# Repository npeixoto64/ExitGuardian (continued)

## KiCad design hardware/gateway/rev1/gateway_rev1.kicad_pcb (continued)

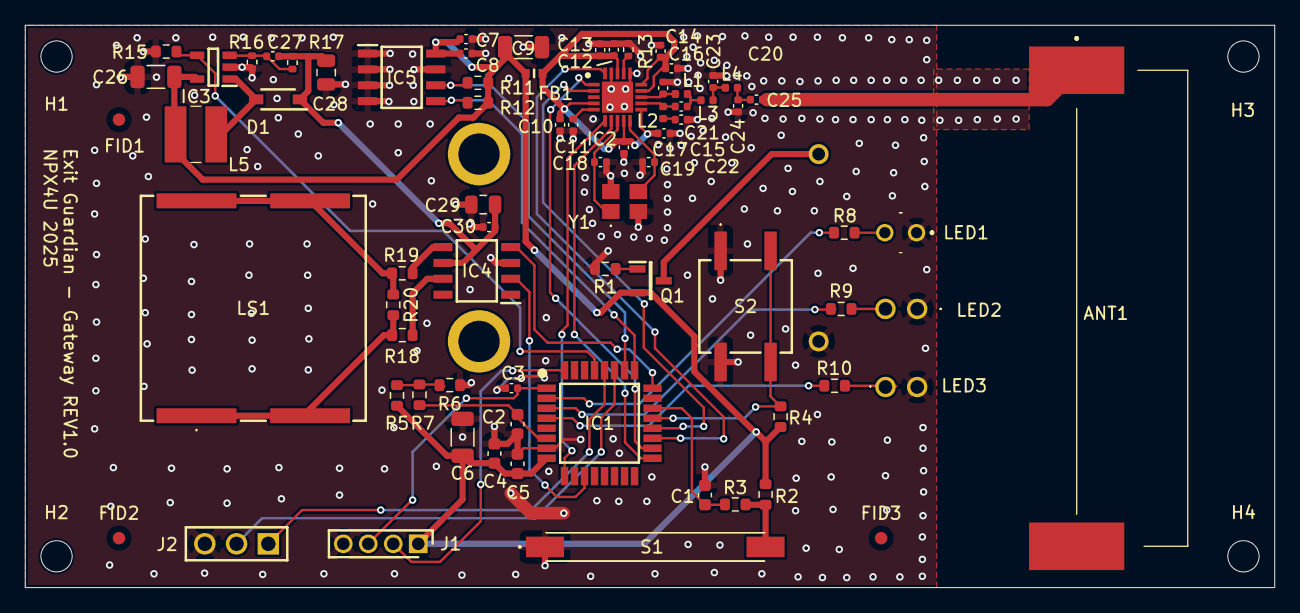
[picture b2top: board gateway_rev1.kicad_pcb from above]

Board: 2 copper layers, 100.0 x 45.0 mm, 80 parts (1 on the bottom side), 48 nets.

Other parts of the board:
FID1, FID2, FID3: Fiducial; Fiducial_1mm_Mask2mm

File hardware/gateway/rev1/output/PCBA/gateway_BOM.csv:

Designator,Qty,Value,Package,Manufacturer,Manufacturer Part Number,Mouser Part Number,Supplier Link
ANT1,1,ANT-433-HESM,MyParts:ANT433HESM,,,712-ANT-433-HESM,
"C1,C2,C5",3,100nF,Capacitor_SMD:C_0603_1608Metric,Taiyo Yuden,MAJCH168BB7104KT,963-MAJCH168BB7104KT,https://pt.mouser.com/ProductDetail/TAIYO-YUDEN/MAJCH168BB71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
C3,1,10nF,Capacitor_SMD:C_0402_1005Metric,Murata,GXT155R71C103KE01D,81-GXT155R71C103KE1D,https://pt.mouser.com/ProductDetail/Murata-Electronics/GXT15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
C4,1,1uF,Capacitor_SMD:C_0603_1608Metric,Yageo,CC603KRX5R6BB105 ,603-CC603KRX5R6BB105 ,https://pt.mouser.com/ProductDetail/YAGEO/CC0603KRX5R6BB105?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
"C6,C9",2,"47uF, 6.3V",Capacitor_SMD:C_1206_3216Metric,TAYO YUDEN,JMK325B7476MM-PR,963-JMK325B7476MM-PR,https://pt.mouser.com/ProductDetail/TAIYO-YUDEN/JMK325B7476M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
"C7,C13",2,1uF,Capacitor_SMD:C_0402_1005Metric,Murata,GXT155R60J105KE01D ,81-GXT155R60J105KE1D,https://pt.mouser.com/ProductDetail/Murata-Electronics/GXT15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
"C8,C10,C11,C12,C14,C15,C16,C17,C30",9,100nF,Capacitor_SMD:C_0402_1005Metric,Yageo,CC0402KRX7R7BB104,603-CC402KRX7R7BB104,https://pt.mouser.com/ProductDetail/YAGEO/CC0402KRX7R7BB104?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
"C18,C19",2,12pF,Capacitor_SMD:C_0402_1005Metric,Murata Electronics,GRM1555C1H120FA1D,81-GRM1555C1H120FA1D,https://pt.mouser.com/ProductDetail/Murata-Electronics/GRM15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
"C20,C22",2,3.9pF,Capacitor_SMD:C_0402_1005Metric,Murata,GRM1555C1E3R9CA1D,81-GRM1555C1E3R9CA1D,https://pt.mouser.com/ProductDetail/Murata-Electronics/GRM15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
"C21,C25",2,220pF,Capacitor_SMD:C_0402_1005Metric,Murata,GRM0225C1C221JA2L,81-GRM0225C1C221JA2L,https://pt.mouser.com/ProductDetail/Murata-Electronics/GRM02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
C23,1,8.2pF,Capacitor_SMD:C_0402_1005Metric,Murata,GCQ0335C1H8R2WB1D,81-GCQ0335C1H8R2WB1D,https://pt.mouser.com/ProductDetail/Murata-Electronics/GCQ03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
C24,1,5.6pF,Capacitor_SMD:C_0402_1005Metric,Murata,GCQ0335C1H5R6BB1D,81-GCQ0335C1H5R6BB1D,https://pt.mouser.com/ProductDetail/Murata-Electronics/GCQ03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
C26,1,"22uF, 6.3V",Capacitor_SMD:C_1206_3216Metric,Murata,GGM31CD70J226KE02L,81-GGM31CD70J226KE2L,https://pt.mouser.com/ProductDetail/Murata-Electronics/GGM31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
C27,1,4.7pF,Capacitor_SMD:C_0402_1005Metric,Murata,GCM1555C2A4R7BE02D,81-GCM1555C2A4R7BE2D,https://pt.mouser.com/ProductDetail/Murata-Electronics/GCM15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
"C28,C29",2,"4.7uF, 25V",Capacitor_SMD:C_0805_2012Metric,Taiyo Yuden,MCAST21GBC7475KTCA01,963-MCAST21GBC7475KT,https://pt.mouser.com/ProductDetail/TAIYO-YUDEN/MCAST21GBC74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
D1,1,MBR0520LT3G,MyParts:SOD3716X135N,onsemi,MBR0520LT3G,863-MBR0520LT3G,https://www.mouser.co.uk/ProductDetail/onsemi/MBR0520LT3G?qs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
FB1,1,BLM18KG601SN1D,MyParts:BLM18SP221SN1B,Murata Electronics,BLM18KG601SN1D,81-BLM18KG601SN1D,https://www.mouser.co.uk/ProductDetail/Murata-Electronics/BL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
IC1,1,STM8L151K4T6,MyParts:QFP80P900X900X160-32N,STMicroelectronics,STM8L151K4T6,511-STM8L151K4T6,https://www.mouser.co.uk/ProductDetail/STMicroelectronics/ST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
IC2,1,CC1101RGPR,MyParts:QFN50P400X400X100-21N-D,Texas Instruments,CC1101RGPR,595-CC1101RGPR,https://www.mouser.co.uk/ProductDetail/Texas-Instruments/CC1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
IC3,1,LT1615ES5-1#TRMPBF,MyParts:SOT95P280X100-5N,Analog Devices,LT1615ES5-1#TRMPBF,584-1615ES5-1TRMPBF,https://www.mouser.co.uk/ProductDetail/Analog-Devices/LT1615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
IC4,1,MIC4427YM,MyParts:SOIC127P599X173-8N,Microchip,MIC4427YM,998-MIC4427YM,https://www.mouser.co.uk/ProductDetail/Microchip-Technology/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
IC5,1,MB85RC64TAPNF-G-BDERE1,MyParts:SOIC127P602X173-8N,Ramxeed,MB85RC64TAPNF-G-BDERE1,249-85C64TAPNFGBDR1,https://www.mouser.co.uk/ProductDetail/Fujitsu-Semiconductor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
J1,1,G8250041000YEU,MyParts:HDRV4W55P0X200_1X4_800X200X635P,Amphenol,G8250041000YEU,523-G8250041000YEU,https://www.mouser.co.uk/ProductDetail/Amphenol-Commercial-P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
J2,1,M20-9770342,MyParts:HDRV3W66P0X254_1X3_762X254X855P,Harwin,M20-9770342,855-M20-9770342,https://www.mouser.co.uk/ProductDetail/Harwin/M20-9770342?qs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
"L1,L2,L4",3,27nH,Inductor_SMD:L_0402_1005Metric,Murata,LQG15HS27NJ02D,81-LQG15HS27NJ02D,https://pt.mouser.com/ProductDetail/Murata-Electronics/LQG15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
L3,1,22nH,Inductor_SMD:L_0402_1005Metric,Murata,LQW15CA22NJ00D,81-LQW15CA22NJ00D,https://pt.mouser.com/ProductDetail/Murata-Electronics/LQW15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
L5,1,CD43NP-100MC,MyParts:CD43NP100MC,Sumida,CD43NP-100MC,851-CD43NP-100MC,https://www.mouser.co.uk/ProductDetail/Sumida/CD43NP-100MC?q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
LED1,1,WP710A10LVBC_D,MyParts:WP710A10LVBCD,Kingbright,WP710A10LVBC/D,604-WP710A10LVBCD,https://www.mouser.co.uk/ProductDetail/Kingbright/WP710A10LV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
LED2,1,TLHY4400-AS12Z,MyParts:TLHY4400AS12Z,Vishay,TLHY4400-AS12Z,78-TLHY4400-AS12Z,https://www.mouser.co.uk/ProductDetail/Vishay-Semiconductors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
LED3,1,TLHR4400-AS12Z,MyParts:TLHR4400AS12Z,Vishay,TLHR4400-AS12Z,78-TLHR4400-AS12Z,https://www.mouser.co.uk/ProductDetail/Vishay-Semiconductors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
LS1,1,PKMCS1818E20A0-R1,MyParts:PKMCS1818E20A0R1,Murata Electronics,PKMCS1818E20A0-R1,81-PKMCS1818E20A0-R1,https://www.mouser.co.uk/ProductDetail/Murata-Electronics/PK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
Q1,1,IRLML6402TRPBF,MyParts:SOT95P237X112-3N,Infineon,IRLML6402TRPBF,942-IRLML6402TRPBF,https://www.mouser.co.uk/ProductDetail/Infineon-Technologies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
"R1,R3,R15",3,100K,Resistor_SMD:R_0603_1608Metric,Vishay,MCT06030C1003FP5,594-MCT06030C1003FP5,https://pt.mouser.com/ProductDetail/Vishay-Beyschlag/MCT0603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
"R2,R5,R20",3,1M,Resistor_SMD:R_0603_1608Metric,Yageo,AR0603FR-071ML,603-AR0603FR-071ML,https://pt.mouser.com/ProductDetail/YAGEO/AR0603FR-071ML?qs=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
"R4,R11,R12",3,10K,Resistor_SMD:R_0603_1608Metric,Vishay,RCA060310K0JNEA,71-RCA060310K0JNEA,https://pt.mouser.com/ProductDetail/Vishay-Draloric/RCA06031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
R6,1,510K,Resistor_SMD:R_0603_1608Metric,Vishay,CRCW0603-510K,71-CRCW0603-510K,https://pt.mouser.com/ProductDetail/Vishay/CRCW0603510KFKTA?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
R7,1,1K,Resistor_SMD:R_0603_1608Metric,Yageo,SR0603JR-071KL,603-SR0603JR-071KL,https://pt.mouser.com/ProductDetail/YAGEO/SR0603JR-071KL?qs=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
R8,1,100,Resistor_SMD:R_0603_1608Metric,Vishay,CRCW0603100RJNEBC,71-CRCW0603100RJNEBC,https://pt.mouser.com/ProductDetail/Vishay/CRCW0603100RJNEBC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
"R9,R10",2,47,Resistor_SMD:R_0603_1608Metric,Panasonic,ERJ-S03J470V,667-ERJ-S03J470V,https://pt.mouser.com/ProductDetail/Panasonic/ERJ-S03J470V?q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
R13,1,56K,Resistor_SMD:R_0402_1005Metric,Panasonic,ERJ-PA2F5602X,667-ERJ-PA2F5602X,https://pt.mouser.com/ProductDetail/Panasonic/ERJ-PA2F5602X?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
R16,1,130K,Resistor_SMD:R_0402_1005Metric,Yageo,RC0402DR-07130KL,603-RC0402DR-07130KL,https://pt.mouser.com/ProductDetail/YAGEO/RC0402DR-07130KL?q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
R17,1,1.15M,Resistor_SMD:R_0402_1005Metric,Yageo,RC0402FR-071M15L,603-RC0402FR-071M15L,https://pt.mouser.com/ProductDetail/YAGEO/RC0402FR-071M15L?q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
"R18,R19",2,33R,Resistor_SMD:R_0603_1608Metric,Yageo,"SR0603JR-7T33RL,SR0603JR-7T33RL ","603-SR0603JR-7T33RL,603-SR0603JR-7T33RL ",https://pt.mouser.com/ProductDetail/YAGEO/SR0603JR-7T33RL?qs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
S1,1,MASM-14R-8-10,MyParts:MASM14R810,LITTELFUSE,MASM-14R-8-10,934-MASM-14R-8-10,https://www.mouser.co.uk/ProductDetail/Littelfuse/MASM-14R-8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
S2,1,TL6120DF160QG,MyParts:TL6120DF160QG,E-Switch,TL6120DF160QG,612-TL6120DF160QG,https://www.mouser.co.uk/ProductDetail/E-Switch/TL6120DF160Q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
U1,1,2462,MyParts:2462,Keystone Electronics,2462,534-2462,https://www.mouser.co.uk/ProductDetail/Keystone-Electronics/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
Y1,1,NX3225GA-26.000M-STD-CRG-2,MyParts:NX3225GA26000MSTDCRG2,NDK,NX3225GA-26.000M-STD-CRG-2,344-NX3225GA26MSTRG2,https://www.mouser.co.uk/ProductDetail/NDK/NX3225GA-26.000M-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

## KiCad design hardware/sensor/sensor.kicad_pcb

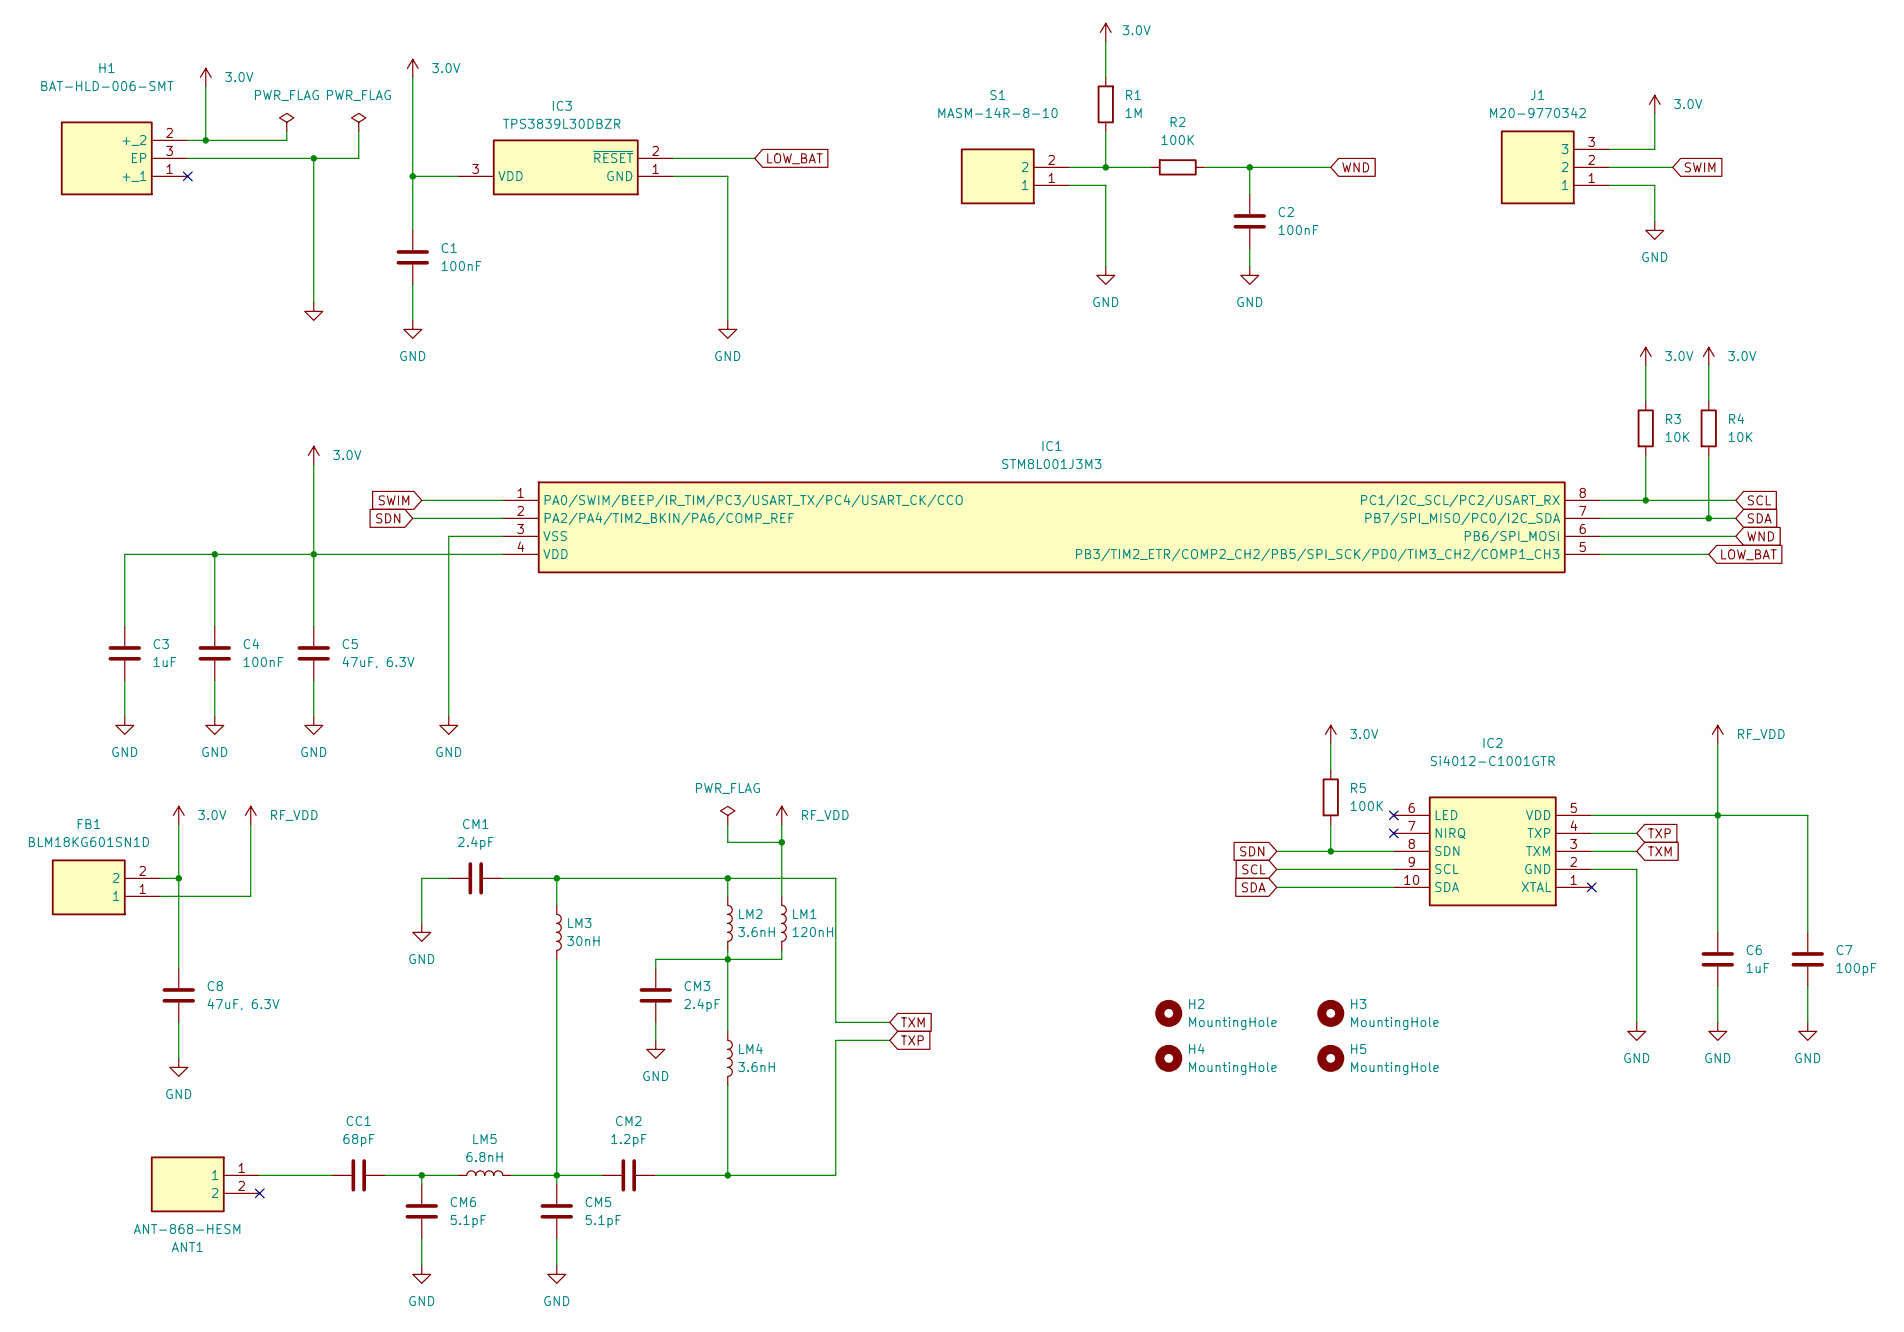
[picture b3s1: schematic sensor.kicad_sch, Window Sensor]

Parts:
ANT1: ANT-868-HESM; Mouser Part Number 712-ANT-868-HESM
C1, C2, C4: 100nF; C_0603_1608Metric; Mouser Part Number 81-GCJ188R72A104KA1D
C3, C6: 1uF; C_0603_1608Metric; Mouser Part Number 963-MBASE168SB7105KT
C5, C8: 47uF, 6.3V; C_1206_3216Metric; Mouser Part Number 963-JMK325B7476MM-PR
C7: 100pF; C_0603_1608Metric; Mouser Part Number 77-VJ0603Y101MXQCBC
CC1: 68pF; C_0402_1005Metric; Mouser Part Number 81-GRM1555C1H680FA1J
CM1, CM3: 2.4pF; C_0402_1005Metric; Mouser Part Number 81-GRM1555C1H2R4WA1D
CM2: 1.2pF; C_0402_1005Metric; Mouser Part Number 81-GRM1555C1H1R2WA1D
CM5, CM6: 5.1pF; C_0402_1005Metric; Mouser Part Number 81-GRM1555C1H5R1WA1D
FB1: BLM18KG601SN1D; BLM18SP221SN1B; Mouser Part Number 81-BLM18KG601SN1D
H1: BAT-HLD-006-SMT; BATHLD006SMT; Mouser Part Number 712-BAT-HLD-006-SMT
H2, H3, H4, H5: MountingHole; MountingHole_2.5mm
IC1: STM8L001J3M3; SOIC127P600X175-8N; Mouser Part Number 511-STM8L001J3M3
IC2: Si4012-C1001GTR; SOP50P490X110-10N; Mouser Part Number 634-SI4012-C1001GTR
IC3: TPS3839L30DBZR; SOT95P237X112-3N; Mouser Part Number 595-TPS3839L30DBZR
J1: M20-9770342; HDRV3W66P0X254_1X3_762X254X855P; Mouser Part Number 855-M20-9770342
LM1: 120nH; L_0603_1608Metric; Mouser Part Number 994-0603HP-R12XGLU
LM2, LM4: 3.6nH; L_0402_1005Metric; Mouser Part Number 994-0402HP-3N6XGRW
LM3: 30nH; L_0402_1005Metric; Mouser Part Number 994-0402HP-30NXJRW
LM5: 6.8nH; L_0402_1005Metric; Mouser Part Number 994-0402HP-6N8XGRW
R1: 1M; R_0603_1608Metric; Mouser Part Number 755-SFR03EZPJ105
R2, R5: 100K; R_0603_1608Metric; Mouser Part Number 71-RCA0603100KJNEA
R3, R4: 10K; R_0603_1608Metric; Mouser Part Number 603-AC0603JR-7W10KL
S1: MASM-14R-8-10; MASM14R810; Mouser Part Number 934-MASM-14R-8-10

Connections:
3.0V: C1.1, C3.1, C4.1, C5.1, C8.1, FB1.2, H1.2 (+_2), IC1.4 (VDD), IC3.3 (VDD), J1.3, R1.2, R3.1, R4.1, R5.1
GND: C1.2, C2.2, C3.2, C4.2, C5.2, C6.2, C7.2, C8.2, CM1.2, CM3.2, CM5.2, CM6.2, H1.3 (EP), IC1.3 (VSS), IC2.2 (GND), IC3.1 (GND), J1.1, S1.1
LOW_BAT: IC1.5 (PB3/TIM2_ETR/COMP2_CH2/PB5/SPI_SCK/PD0/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), IC3.2 (~RESET)
unnamed: ANT1.1, CC1.1
unnamed: CC1.2, CM6.1, LM5.1
unnamed: CM2.1, CM5.1, LM3.2, LM5.2
unnamed: CM3.1, LM1.2, LM2.2, LM4.1
unnamed: R1.1, R2.2, S1.2
RF_VDD: C6.1, C7.1, FB1.1, IC2.5 (VDD), LM1.1
SCL: IC1.8 (PC1/I2C_SCL/PC2/USART_RX), IC2.9 (SCL), R3.2
SDA: IC1.7 (PB7/SPI_MISO/PC0/I2C_SDA), IC2.10 (SDA), R4.2
SDN: IC1.2 (PA2/PA4/TIM2_BKIN/PA6/COMP_REF), IC2.8 (SDN), R5.2
SWIM: IC1.1 (PA0/SWIM/BEEP/IR_TIM/PC3/USART_TX/PC4/U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), J1.2
TXM: CM1.1, IC2.3 (TXM), LM2.1, LM3.1
TXP: CM2.2, IC2.4 (TXP), LM4.2
WND: C2.1, IC1.6 (PB6/SPI_MOSI), R2.1

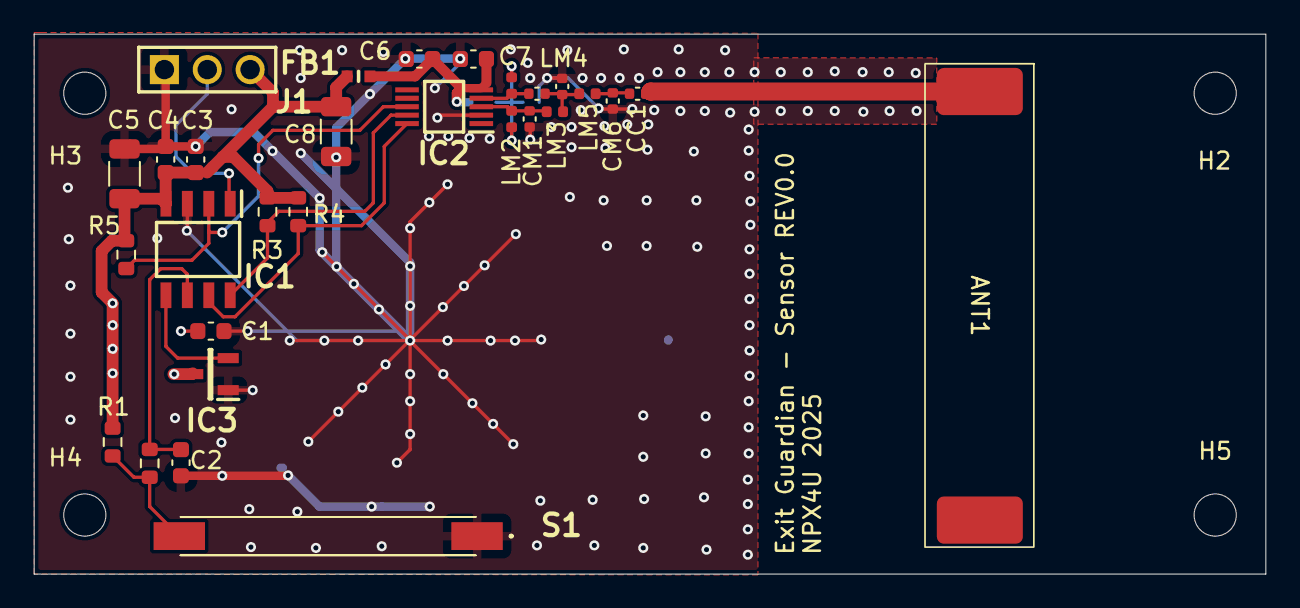
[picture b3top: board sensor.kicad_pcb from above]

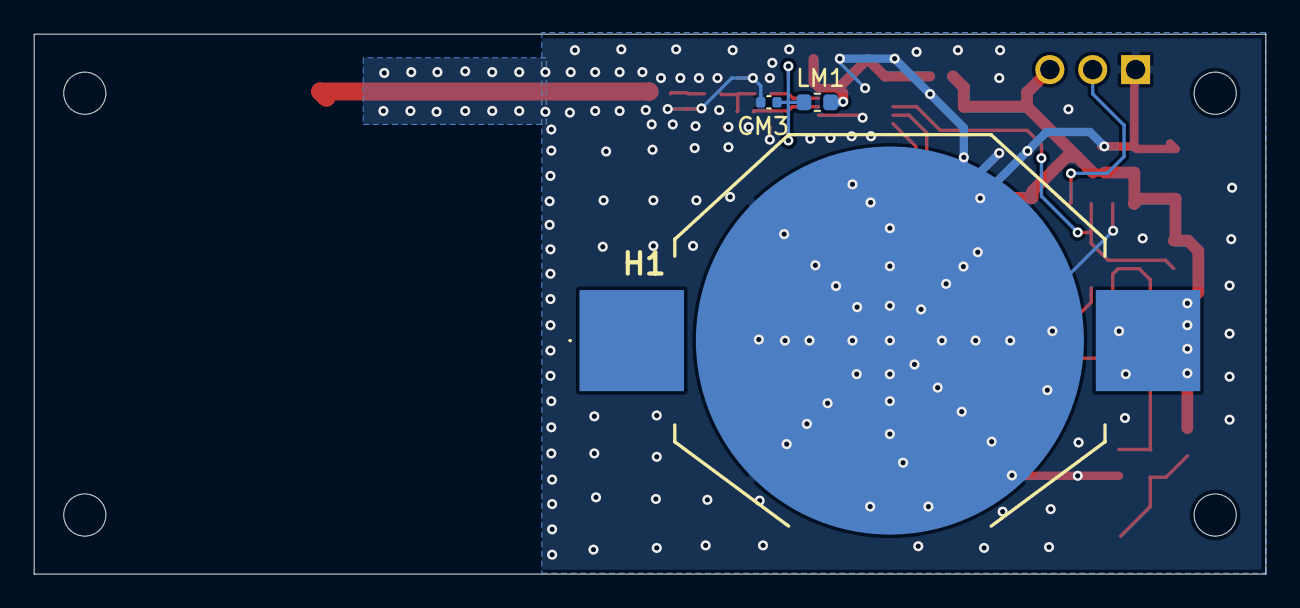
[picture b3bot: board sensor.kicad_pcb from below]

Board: 2 copper layers, 73.0 x 32.0 mm, 36 parts (3 on the bottom side), 16 nets.

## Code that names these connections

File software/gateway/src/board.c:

/**
 * @file board.c
 * @brief Board support package implementation: clocks, peripherals and power.
 */
#include "board.h"

#include "stm8l15x_clk.h"
#include "stm8l15x_gpio.h"
#include "stm8l15x_adc.h"
#include "stm8l15x_i2c.h"
#include "stm8l15x_spi.h"
#include "stm8l15x_usart.h"
#include "stm8l15x_tim1.h"
#include "stm8l15x_tim4.h"
#include "stm8l15x_exti.h"
#include "stm8l15x_iwdg.h"
#include "cc1101.h"

/** @brief Configure the system clock to 16 MHz from the internal HSI. */
static void clock_init(void)
{
  /* 16 MHz (HSI with divider 1) */
  CLK_HSICmd(ENABLE);
  while (CLK_GetFlagStatus(CLK_FLAG_HSIRDY) == RESET);
  CLK_SYSCLKSourceConfig(CLK_SYSCLKSource_HSI);
  CLK_SYSCLKDivConfig(CLK_SYSCLKDiv_1);
}

/**
 * @brief Configure all GPIOs used on the board.
 *
 * Unused pins are pulled up to minimise leakage; peripheral pins are set to
 * the modes required by I2C, SPI, USART, TIM1 PWM and the EXTI inputs.
 */
static void gpio_init(void)
{
  /* Unused pins as input pull-up to minimise leakage. */
  GPIO_Init(GPIOA, GPIO_Pin_5, GPIO_Mode_In_PU_No_IT);
  GPIO_Init(GPIOB, GPIO_Pin_0, GPIO_Mode_In_PU_No_IT);
  GPIO_Init(GPIOB, GPIO_Pin_1, GPIO_Mode_In_PU_No_IT);
  GPIO_Init(GPIOB, GPIO_Pin_2, GPIO_Mode_In_PU_No_IT);
  GPIO_Init(GPIOB, GPIO_Pin_3, GPIO_Mode_In_PU_No_IT);
  GPIO_Init(GPIOC, GPIO_Pin_5, GPIO_Mode_In_PU_No_IT);
  GPIO_Init(GPIOC, GPIO_Pin_6, GPIO_Mode_In_PU_No_IT);
  GPIO_Init(GPIOD, GPIO_Pin_6, GPIO_Mode_In_PU_No_IT);

  /* PA6 ADC input (floating). */
  GPIO_Init(GPIOA, GPIO_Pin_6, GPIO_Mode_In_FL_No_IT);

  /* I2C: PC0 SDA, PC1 SCL (open-drain). */
  GPIO_Init(GPIOC, GPIO_Pin_0, GPIO_Mode_Out_OD_HiZ_Fast);
  GPIO_Init(GPIOC, GPIO_Pin_1, GPIO_Mode_Out_OD_HiZ_Fast);

  /* SPI: PB4 NSS, PB5 SCK, PB6 MOSI, PB7 MISO. */
  GPIO_Init(GPIOB, GPIO_Pin_4, GPIO_Mode_Out_PP_High_Fast);
  GPIO_Init(GPIOB, GPIO_Pin_5, GPIO_Mode_Out_PP_High_Fast);
  GPIO_Init(GPIOB, GPIO_Pin_6, GPIO_Mode_Out_PP_High_Fast);
  GPIO_Init(GPIOB, GPIO_Pin_7, GPIO_Mode_In_FL_No_IT);

  /* USART: PC2 TX, PC3 RX. */
  GPIO_Init(GPIOC, GPIO_Pin_2, GPIO_Mode_Out_PP_High_Fast);
  GPIO_Init(GPIOC, GPIO_Pin_3, GPIO_Mode_In_FL_No_IT);

  /* TIM1 differential PWM: PD7 CH1, PD2 CH1N. */
  GPIO_Init(GPIOD, GPIO_Pin_7, GPIO_Mode_Out_PP_High_Fast);
  GPIO_Init(GPIOD, GPIO_Pin_2, GPIO_Mode_Out_PP_High_Fast);

  /* External interrupt inputs. */
  GPIO_Init(IRQ_CC1101_PORT, IRQ_CC1101_PIN, GPIO_Mode_In_FL_IT);
  GPIO_Init(PUSH_BTN_PORT,   PUSH_BTN_PIN,   GPIO_Mode_In_FL_IT);
  GPIO_Init(REED_DOOR_PORT,  REED_DOOR_PIN,  GPIO_Mode_In_FL_IT);

  /* LEDs + spare PC4 output. */
  GPIO_Init(LED_B_PORT, LED_B_PIN, GPIO_Mode_Out_PP_Low_Fast);
  GPIO_Init(LED_Y_PORT, LED_Y_PIN, GPIO_Mode_Out_PP_Low_Fast);
  GPIO_Init(LED_R_PORT, LED_R_PIN, GPIO_Mode_Out_PP_Low_Fast);
  GPIO_Init(BUZZER_EN_PORT, BUZZER_EN_PIN, GPIO_Mode_Out_PP_Low_Fast);

  GPIO_ResetBits(LED_B_PORT, LED_B_PIN);
  GPIO_ResetBits(LED_Y_PORT, LED_Y_PIN);
  GPIO_ResetBits(LED_R_PORT, LED_R_PIN);
  GPIO_ResetBits(BUZZER_EN_PORT, BUZZER_EN_PIN);
}

/** @brief Configure EXTI edge sensitivity for CC1101, button and reed inputs. */
static void exti_init(void)
{
  EXTI_SetPinSensitivity(IRQ_CC1101_EXTI, EXTI_Trigger_Falling);
  EXTI_SetPinSensitivity(PUSH_BTN_EXTI,   EXTI_Trigger_Rising_Falling);
  EXTI_SetPinSensitivity(REED_DOOR_EXTI,  EXTI_Trigger_Rising_Falling);
}

/** @brief Millisecond tick counter, incremented by @ref board_systick_irq. */
static volatile uint16_t s_tick_ms = 0;

/** @brief Configure TIM4 to generate a 1 kHz periodic update interrupt. */
static void systick_init(void)
{
  /* 16 MHz / 128 = 125 kHz; period 125 -> 1 ms tick. */
  CLK_PeripheralClockConfig(CLK_Peripheral_TIM4, ENABLE);
  TIM4_DeInit();
  TIM4_TimeBaseInit(TIM4_Prescaler_128, 125U - 1U);
  TIM4_ClearITPendingBit(TIM4_IT_Update);
  TIM4_ITConfig(TIM4_IT_Update, ENABLE);
  TIM4_Cmd(ENABLE);
}

uint16_t board_get_tick_ms(void)
{
  uint16_t t;
  /* Atomic read: save CC (I0/I1), mask interrupts, restore on exit.
   * Safe to call from both thread and ISR context. */
  __asm__("push cc\n\tsim");
  t = s_tick_ms;
  __asm__("pop cc");
  return t;
}

void board_systick_irq(void)
{
  TIM4_ClearITPendingBit(TIM4_IT_Update);
  s_tick_ms++;
}

/** @brief Configure ADC1 single-conversion mode on channel 6 (PA6). */
static void adc_init(void)
{
  CLK_PeripheralClockConfig(CLK_Peripheral_ADC1, ENABLE);
  ADC_DeInit(ADC1);
  ADC_Init(ADC1, ADC_ConversionMode_Single, ADC_Resolution_12Bit, ADC_Prescaler_2);
  ADC_SamplingTimeConfig(ADC1, ADC_Group_SlowChannels, ADC_SamplingTime_384Cycles);
  ADC_Cmd(ADC1, ENABLE);
  ADC_ChannelCmd(ADC1, ADC_Channel_6, ENABLE);
}

/** @brief Configure I2C1 as master at 400 kHz for the FRAM device. */
static void i2c_init(void)
{
  CLK_PeripheralClockConfig(CLK_Peripheral_I2C1, ENABLE);
  I2C_DeInit(I2C1);
  I2C_Init(I2C1, 400000, 0x00, I2C_Mode_I2C, I2C_DutyCycle_2,
           I2C_Ack_Enable, I2C_AcknowledgedAddress_7bit);
  I2C_Cmd(I2C1, ENABLE);
}

/** @brief Configure SPI1 as 8-bit master, mode 0, for the CC1101. */
static void spi_init(void)
{
  CLK_PeripheralClockConfig(CLK_Peripheral_SPI1, ENABLE);
  SPI_DeInit(SPI1);
  SPI_Init(SPI1, SPI_FirstBit_MSB, SPI_BaudRatePrescaler_16, SPI_Mode_Master,
           SPI_CPOL_Low, SPI_CPHA_1Edge, SPI_Direction_2Lines_FullDuplex,
           SPI_NSS_Soft, 7);
  SPI_Cmd(SPI1, ENABLE);
}

/** @brief Configure USART1 for 9600 8N1 debug logging. */
static void uart_init(void)
{
  CLK_PeripheralClockConfig(CLK_Peripheral_USART1, ENABLE);
  USART_DeInit(USART1);
  USART_Init(USART1, (uint32_t)9600, USART_WordLength_8b, USART_StopBits_1,
             USART_Parity_No,
             (USART_Mode_TypeDef)(USART_Mode_Tx | USART_Mode_Rx));
  USART_Cmd(USART1, ENABLE);
}

/** @brief Configure TIM1 channel 1 / 1N differential PWM for the buzzer. */
static void pwm_init(void)
{
  CLK_PeripheralClockConfig(CLK_Peripheral_TIM1, ENABLE);
  TIM1_DeInit();
  TIM1_TimeBaseInit(7U, TIM1_CounterMode_Up, 1000U, 0U);
  TIM1_OC1Init(TIM1_OCMode_PWM1,
               TIM1_OutputState_Enable,
               TIM1_OutputNState_Enable,
               500U,
               TIM1_OCPolarity_High,
               TIM1_OCNPolarity_High,
               TIM1_OCIdleState_Reset,
               TIM1_OCNIdleState_Reset);
  TIM1_OC1PreloadConfig(ENABLE);
  TIM1_BDTRConfig(TIM1_OSSIState_Disable,
                  TIM1_LockLevel_Off,
                  0x10U,
                  TIM1_BreakState_Disable,
                  TIM1_BreakPolarity_Low,
                  TIM1_AutomaticOutput_Disable);
  TIM1_CtrlPWMOutputs(ENABLE);
}

/** @brief Start the independent watchdog with ~1.72 s timeout. */
static void iwdg_init(void)
{
  /* LSI is ~38 kHz. With prescaler 256 the IWDG tick is ~6.74 ms.
   * Reload 0xFF gives a watchdog timeout of ~1.72 s. */
  IWDG_Enable();
  IWDG_WriteAccessCmd(IWDG_WriteAccess_Enable);
  IWDG_SetPrescaler(IWDG_Prescaler_256);
  IWDG_SetReload(0xFF);
  IWDG_ReloadCounter();
}

void board_iwdg_refresh(void)
{
  IWDG_ReloadCounter();
}

void board_init(void)
{
  clock_init();
  gpio_init();
  exti_init();
  adc_init();
  i2c_init();
  spi_init();
  uart_init();
  pwm_init();
  systick_init();
  iwdg_init();

  enableInterrupts();
  
  cc1101_config_gfsk_433_rx_fixed(5);
}

void board_buzzer(uint8_t on)
{
  TIM1_Cmd(on ? ENABLE : DISABLE);
}

void board_enter_deep_sleep(void)
{
  /* Reduce current draw before HALT; wake source is EXTI on PD0/PD4/PD5. */
  ADC_Cmd(ADC1, DISABLE);
  I2C_Cmd(I2C1, DISABLE);
  SPI_Cmd(SPI1, DISABLE);
  USART_Cmd(USART1, DISABLE);

  enableInterrupts();
  halt();

  /* Restore peripherals after wake-up. */
  CLK_PeripheralClockConfig(CLK_Peripheral_ADC1, ENABLE);
  CLK_PeripheralClockConfig(CLK_Peripheral_I2C1, ENABLE);
  CLK_PeripheralClockConfig(CLK_Peripheral_SPI1, ENABLE);
  CLK_PeripheralClockConfig(CLK_Peripheral_USART1, ENABLE);
  CLK_PeripheralClockConfig(CLK_Peripheral_TIM1, ENABLE);

  ADC_Cmd(ADC1, ENABLE);
  I2C_Cmd(I2C1, ENABLE);
  SPI_Cmd(SPI1, ENABLE);
  USART_Cmd(USART1, ENABLE);
}

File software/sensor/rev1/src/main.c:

/**
 * @file main.c
 * @brief Application entry point and top-level interrupt handlers.
 */
#include <stdint.h>
#include <stdio.h>
#include "stm8l15x_itc.h"
#include "board.h"
#include "device_id.h"
#include "app_config.h"
#include "stm8l15x_gpio.h"
#include "stm8l15x_exti.h"
#include "stm8l15x_tim4.h"
#include "cc1101.h"
#include "log.h"

// ============================================================================
// Constants and Enums
// ============================================================================

// Status byte format:
// Bits 7-4: Battery capacity (high nibble)
// Bits 2-1: Button action (2 bits): 0=none, 1=force update, 2=pair, 3=unpair
// Bit 0:    Reed switch state
#define STATUS_REED_SW_BIT      0
#define STATUS_BTN_SHIFT        1
#define STATUS_BTN_MASK         0x03
#define STATUS_BATT_SHIFT       4
#define STATUS_BATT_MASK        0x0F

#define STATUS_SET_BATT(batt)   (((batt) & STATUS_BATT_MASK) << STATUS_BATT_SHIFT)
#define STATUS_SET_BTN(btn)     (((btn) & STATUS_BTN_MASK) << STATUS_BTN_SHIFT)
#define STATUS_SET_REED(reed)   (((reed) ? 1 : 0) << STATUS_REED_SW_BIT)

typedef enum {
    BTN_ACTION_NONE       = 0,
    BTN_ACTION_FORCE_UPD  = 1,
    BTN_ACTION_PAIR       = 2,
    BTN_ACTION_UNPAIR     = 3,
} button_action_t;

// Timing constants (in TIM2 ticks, 10ms per tick)
#define DEBOUNCE_TICKS              3    // 30ms debounce period
#define BTN_DOUBLE_PRESS_WINDOW     40   // 400ms max gap between clicks
#define BTN_LONG_PRESS_TICKS        80   // 800ms hold duration
#define LED_ON_HOLD_TICKS           50   // 500ms before auto-off
#define LED_ON_STARTUP_HOLD_TICKS   100  // 1000ms startup hold
#define LED_BLINK_HALF_PERIOD       20   // 200ms half-period for blink
#define LED_BLINK_COUNT             4    // 4 on-off cycles for low battery
#define LOW_BATTERY_THRESHOLD       3    // 0-15 scale
#define WWDG_COUNTER_MAX            0x7F // WWDG 7-bit counter max value (T[6:0])
#define WWDG_REFRESH_THRESHOLD      0x40 // Latest safe refresh point before watchdog reset (counter must stay >= 0x40)

// ============================================================================
// Global System State
// ============================================================================

static volatile uint8_t g_tim2_ticks = 0xFF;

// Button state variables
static struct {
    volatile uint8_t irq_flag;
    volatile uint8_t last_irq_tick;
    uint8_t is_pressed;
    uint8_t press_start_tick;
    uint8_t click_count;
    uint8_t first_click_tick;
    uint8_t long_press_reported;
} g_button = {0};

// LED state variables
static struct {
    uint8_t is_on;
    uint8_t off_flag;
    uint8_t on_start_tick;
    uint8_t blink_remaining;
    uint8_t blink_last_toggle_tick;
} g_led = {0};

// Reed switch state variables
static struct {
    volatile uint8_t irq_flag;
    volatile uint8_t last_irq_tick;
    uint8_t current_state;
} g_reed = {0};

// Power management state
static struct {
    volatile uint8_t gdo0_tx_complete_flag;
} g_power = {0};

uint32_t chip_id_hash = 0;

// ============================================================================
// Utility Functions
// ============================================================================

static inline uint8_t ticks_elapsed_since(uint8_t tick_start)
{
    return (uint8_t)(tick_start - g_tim2_ticks);
}

// ============================================================================
// LED Control
// ============================================================================

static inline void led_turn_on(void)
{
    GPIO_SetBits(GPIOB, GPIO_Pin_0);
    g_led.is_on = 1;
    g_led.on_start_tick = g_tim2_ticks;
    g_led.off_flag = 0;
}

static inline void led_turn_off(void)
{
    GPIO_ResetBits(GPIOB, GPIO_Pin_0);
    g_led.is_on = 0;
    g_led.off_flag = 1;
}

static void led_hold_on_for_duration(uint8_t duration_ticks)
{
    led_turn_on();
    while (ticks_elapsed_since(g_led.on_start_tick) < duration_ticks) {}
}

static void led_update(uint8_t battery_capacity)
{
    if (battery_capacity > LOW_BATTERY_THRESHOLD)
    {
        // Normal battery: single on/off control
        if (g_led.is_on && (ticks_elapsed_since(g_led.on_start_tick) >= LED_ON_HOLD_TICKS))
        {
            led_turn_off();
        }
    }
}

// ============================================================================
// Sensor Communication
// ============================================================================

#ifdef DEBUG
static void log_sensor_status(uint8_t battery_capacity, button_action_t btn_action, uint8_t reed_state)
{
    send_string("\r\n[batt:");
    send_uint8_t(battery_capacity);
    send_string(" btn:");
    send_uint8_t(btn_action);
    send_string(" reed:");
    send_uint8_t(reed_state);
    send_string("] ");
}
#else
#define log_sensor_status(batt, btn, reed)
#define log_battery_level(raw, level)
#endif

static void transmit_sensor_status(uint32_t value)
{
    cc1101_send_msg(value);
    send_string("\r\nSend packet: 0x");
    send_hex_byte((value >> 24) & 0xFF);
    send_hex_byte((value >> 16) & 0xFF);
    send_hex_byte((value >> 8) & 0xFF);
    send_hex_byte(value & 0xFF);
}

static volatile uint8_t  g_irq_cc1101_flag = 0;

/* CC1101 GDO0 falling-edge interrupt (IRQ vector 9, PB1).
 * Set when the CC1101 asserts its interrupt line (active-low),
 * signalling that a packet has been received. Processed in main loop. */
INTERRUPT_HANDLER(EXTI1_IRQHandler, EXTI1_IRQn)
{
  if (GPIO_ReadInputDataBit(GPIOB, GPIO_Pin_1) == RESET)
  {
    g_irq_cc1101_flag = 1;
  }
  EXTI_ClearITPendingBit(EXTI_IT_Pin1);
}

/* Push-button both-edges interrupt (IRQ vector 11, PA3).
 * ISR kept in main.c so the linker always includes button.rel via button_isr(). */
INTERRUPT_HANDLER(EXTI3_IRQHandler, EXTI3_IRQn)
{
  //button_isr();
  GPIO_ToggleBits(GPIOB, GPIO_Pin_0);
  EXTI_ClearITPendingBit(EXTI_IT_Pin3);
}

// /* Reed switch (door sensor) both-edges interrupt (IRQ vector 13, PD5).
//  * ISR kept in main.c so the linker always includes reed.rel via reed_isr(). */
// INTERRUPT_HANDLER(EXTI5_IRQHandler, 13)
// {
//   reed_isr();
//   EXTI_ClearITPendingBit(EXTI_IT_Pin5);
// }

/* TIM4 update/overflow interrupt (IRQ vector 25).
 * Fires at 1 kHz; delegates tick increment and flag clear to board driver.
 * 1 ms tick */
INTERRUPT_HANDLER(TIM4_UPD_OVF_TRG_IRQHandler, TIM4_UPD_OVF_TRG_IRQn)
{
  g_tim2_ticks--;
  TIM4_ClearITPendingBit(TIM4_IT_Update);
}

static void system_initialize(void)
{
    mcu_init();

#ifdef TRANSMITTER
    send_string("\r\n\r\n\r\n**** start [TX MODE] ****");
    board_pre_init_tx();
 #else
    send_string("\r\n\r\n\r\n**** start [RX MODE] ****");
    board_pre_init_rx();
#endif
}

/**
 * @brief Application entry point.
 *
 * Brings up the board and the mode manager, then runs the main super-loop:
 * watchdog refresh, reed/button handling, CC1101 packet dispatch, event
 * forwarding to the mode manager and LED/buzzer tick.
 *
 * @return Never returns.
 */
int main(void)
{
    system_initialize();

    enableInterrupts();

    // LED startup sequence
    led_hold_on_for_duration(LED_ON_STARTUP_HOLD_TICKS);
    //led_turn_off();
    send_string("\r\nled_turn_off()");

    // Initialize system state
    chip_id_hash = device_id_get_hash();
    //g_reed.current_state = (GPIO_ReadInputPin(GPIOA, GPIO_Pin_2) != 0) ? 1 : 0;

    uint32_t counter = 0;

    while (1)
    {
        uint8_t battery_capacity = 10;
        uint8_t timer = g_tim2_ticks;

        // Process button input
#ifdef TRANSMITTER
        transmit_sensor_status(counter++);
#endif

        // Handle radio transmission completion
        if (g_irq_cc1101_flag)
        {
            g_irq_cc1101_flag = 0;
#ifndef TRANSMITTER
            cc1101_recv_msg(&counter);
            send_string("\r\nReceived packet: 0x");
            send_hex_byte((counter >> 24) & 0xFF);
            send_hex_byte((counter >> 16) & 0xFF);
            send_hex_byte((counter >> 8) & 0xFF);
            send_hex_byte(counter & 0xFF);
            send_string("\r\nRX done");
#else
            send_string("\r\nTX done");
#endif
        }

        //GPIO_ToggleBits(GPIOB, GPIO_Pin_0);

        timer = g_tim2_ticks;
        while (ticks_elapsed_since(timer) < LED_ON_STARTUP_HOLD_TICKS) {}
    }
}

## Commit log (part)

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2025-09-10 Update README.md
    Initial project description.
2025-09-10 EG-26 Initial Project Setup
2025-09-11 EG-23 Add project requirements documentation without review.
2025-09-11 EG-23 Identification of requirements and grammar errors fixed.
2025-09-11 EG-23 After review from AI Agent.
2025-09-11 EG-23 Second step review by human.
2025-09-11 EG-23 Improvements from AI agent.
2025-09-11 EG-23 Final review, adding the state remove-sensors.
2025-09-16 EG-23 Removed contradiction regarding the unpairing sensors and factory reset.
2025-09-16 EG-23 Glossary added.
2025-09-16 EG-24 First version of overall system architecture.
2025-09-16 EG-24 Fixed the gateway arch and the alert sequence diagram.
2025-09-17 EG 24 State machine fixed, can be shown in PlantUML preview.
2025-09-17 EG-24 Fixed the supply to external 5V DC instead of 230V AC.
2025-09-18 EG-24 Added system context and high level description diagrams, added the RF sequence diagram and a high level state machine.
2025-09-18 EG-27 First version of sphinx generated documentation working.
2025-09-18 EG-27 Added the main architectural artifacts to documentation.
2025-09-18 EG-27 Requirements markdown file changed in a structured manner to be able to be used by sphinx-myst.
2025-09-18 EG-21 KiCad project creation.
2025-09-19 EG-21 MCU on schematic.
2025-09-19 EG-21 Added datasheets and the main ICs to KiCad project library, including symbol, footprint and 3D model.
2025-09-22 EG-28 Sensor will use an MCU and firmware.
2025-09-22 EG-21 Main components on schematic. Only missing I2C resistors, antenna, MCU RESET signal handling and signals MCU<->Si4012.
2025-09-23 EG-21 Added all components except the antenna balun and antenna footprint. Added the Si4012 antenna application note.
2025-09-23 EG-21 Antenna and programming headers added. Missing the balun part and test points.
2025-09-24 EG-21 Balun, pi-matching and antenna connected.
2025-09-25 EG-21 Schematic complete, without ERC errors. All components updated in the PCB.
2025-09-25 EG-21 All components information inserted. BOM generated.
2025-09-25 EG-22 Components added to the PCB, no connections, not final position.
2025-09-25 EG-22 DRC configuration for Eurocircuits.
2025-09-25 EG-22 Major (bigger) components placed. Missing the balun and antenna pi-matching circuit.
2025-09-26 EG-22 All components placed, battery counter yard changed. No connections, and not final places for all components.
2025-09-26 EG-22 Created a folder just for application notes and moved them from datasheets folder.
2025-09-28 EG-22 All components places frozen. No connections yet.
2025-09-28 EG-22 All Components connected, except ground and VDD, RF_VDD planes and CPWG to antenna.
2025-09-29 EG-22 All connections, including antenna path and ground planes. Only vias are missing between groud planes.
2025-09-29 EG-22 All vias placed.
2025-09-30 EG-11 Design Decisions file, still a draft.
2025-09-30 EG-11 Addded the KiCad project for gateway, with the main components added to library and refasctored the datasheets folder.
2025-09-30 EG-11 Architecture update.
2025-09-30 EG-11 Preliminary BOM defined on design decisions.
2025-10-02 EG-11 Polarity inversion, MCU in and out interfaces connected, including buzzer driver circuit.
2025-10-03 EG-11 All components connected in all sheets. The MCU pin mapping needs to be fixed. The BOM needs to be created. The FRAM need needs to be assessed.
2025-10-03 EG-11 FRAM included, MCU pin mapping finished. Only BOM is not finished.
2025-10-04 EG-11 Changed the MCU from ATtiny to STML8 due to minimum supply voltage.
2025-10-05 EG-11 All connections finished. BOM not created yet.
2025-10-06 EG-11 BOM generated.
2025-10-06 EG-11 ERC passed.
2025-10-06 EG-30 Requirements and architecture update due to design changes.
2025-10-06 EG-30 Include the design decisions on generated documentation.
2025-10-07 EG-29 MCU changed on schematic.
2025-10-07 EG-29 MCU changed on PCB and antenna distance fixed.
2025-10-07 EG-32 Sensor box found and version updated on PCB silk screen.
2025-10-07 EG-12 Components placed without connections. Balun components place needs to be fixed.
2025-10-08 EG-12 Adaption of components places.
2025-10-08 EG-32 Silk screen changed and box sizes added to design decisions file.
2025-10-09 EG-12 Options for gateway enclosure.
2025-10-09 EG-32 Adapted the sensor PCB for SIC5-9-2W enclosure, mainly place the holes and adjust the size of the PCB.
2025-10-09 EG-32 Added the FreeCad project with only the PCB.
2025-10-09 EG-32 3D model of the enclosure with the PCB inside.
2025-10-10 EG-12 All components placed. RF connected, except antenna. Buzzer connected, buzzer power supply connected, FRAM connected. Majority os MCU connections missing.
2025-10-14 EG-12 All components connected, except antenna and ground plane.
2025-10-14 EG-12 GND disconnected and ground plane created. Still changes to be done on power lines and GND.
2025-10-15 EG-12 Fixes on SPI signals and ground planes. Antenna connected with Coplanar wavelenght. Only missing vias to connect grounds and run the DRC.
2025-10-15 EG-12 All DRC erros and warnings fixed. Only missing the vias connecting the ground planes.
2025-10-15 EG-12 Vias inserted to connecvt both ground planes (top and bottom). No DRC errors. All done.
2025-10-16 EG-31 Project with the electronics enclosure and PCB on FreeCad.
2025-10-16 EG-34 PCB antenna PI removed and added vias to connect ground planes on battery holder place.
2025-10-16 EG-33 Added the revision and name of the board on silkscreen.
2025-10-16 EG-34 Fixed the revision and PCB name on silkscreen.
2025-10-16 EG-37 Gerbers, drills, position and BOM generated.
2025-10-16 EG-27 Some RF passive components replaced due to lack of stock. BOM updated.
2025-10-17 EG-37 BOM and gerbers generated due to components replacement.
2025-10-17 EG-37 Gerbers, BOM and CPL reviewed.
2025-10-19 EG-38 Changed the output fabrics location.
2025-10-19 EG-38 Replaced all BOM field names to proper ones, according with manufacturer standards.
2025-10-19 EG-38 BOM fixed: Choosed the same suppliers for 4 components.
2025-10-19 EG-38 BOM re-generated to update the components witrh the same supplier fix.
2025-10-19 EG-38 Gerbers generated.
2025-10-20 Created REV0 without open with KiCad
2025-10-20 Parent folder changed to REV0, without errors.
2025-10-20 REV1 ready
2025-10-20 Changed all references from REV0 to REV1 and update PCB silk screen.
2025-10-20 Schematic adapted for 433 MHz.
2025-10-20 RF passive components placed in the right relative positions.
2025-10-20 All connections performed. Still with DRC errors on antenna footprint.
2025-10-20 All connections finished, no DRC erros, gerbers and, components position and BOM generated.
2025-10-20 Added the 3 fiducial points for pick and place machine.
2025-10-21 Replaced 0402 by 0603 package where was possible.
2025-10-21 DRC errors fixed and silkscreen fixed.
2025-10-21 Changed the paramerters to meet JLCPBC manufacturer capabilities.
2025-10-21 Ready for production, with all fabric outputs generated.
2025-10-23 BOM fixed and finance updated
2025-12-29 Expenses update and chinese transmitters decided.
2025-12-29 EG-39 Project infrastructure setup, compiling and flashing, but no LEDs enabled. Don't know if it reaches main
2026-01-01 EG-39 An LED blinking is working on target, from reset vector to main.
2026-01-03 EG-39 Removed the *.s files. The global variables are still not being assigned. I have to assign them on main.
2026-01-03 EG-39 Debug and Release builds defined in CMakeList.txt.
2026-01-03 EG-40 Included all peripheral drivers. Only clk driver working, setting the sysclk to 16 MHz.
2026-01-04 EG-40 MCU device drivers are integrated. Not all tested so far. Need to test I2C, SPI, UART and ADC.
2026-03-01 First version of CC1101 working in OOK.
2026-03-03 Packet being received by CC1101
2026-03-05 Receiving 4 bytes through CC1101.
2026-03-15 EG-47 Receiving the transmitter ID and the status.
2026-03-15 FeRAM basic test.
2026-03-17 Create the FERAM driver.
2026-03-17 Created the sensor manager SW module.
2026-03-17 Optimization of sensor manager, remove multiplication and base address sum, because it's always 0.
2026-03-19 First version of sensor manager, without review.
2026-03-21 Sensor Manager, first version, not tested.
2026-03-21 EG-14 Enable the beep toggle for every packet received.
2026-03-21 EG-23 Added the function to check for window sensors in open state.
2026-03-21 EG-2 Just MCU in sleep until a radio package is received.
2026-04-21 EG-34 Update the system requirements for REV2.0 sensors and gateway with AC-DC power supply.
2026-04-21 EG-34 Fixed requirements IDs, duplicated and missing ones.
2026-04-21 EG-34 Add an Agent to review requirements.
2026-04-26 EG-34 Fix typos and improve clarity in system requirements documentation
2026-04-26 Update system requirements for sensor reporting and gateway functionality
2026-04-26 EG-34 Update system requirements to version 2.0.0 and enhance clarity in sensor and gateway functionalities
2026-04-26 EG-22 Enhance gateway functionality by adding input and LED aliases, and updating interrupt handlers for button and door sensors. Remove unused vector table file.
2026-04-26 EG-22 Add board initialization and interrupt handling functionality; include LED and input aliases
2026-05-01 EG-22 Button up and down events detected with debounce being handled.
2026-05-01 EG-22 Reed switch handled with debounce.
2026-05-01 EG-22 Button functionality implemented.
2026-05-01 EG-22 Moved the reed handle code to an isolated file.
2026-05-01 EG-22 Button code moved to button SW module.
2026-05-02 EG-22 Moved the blue LED code to Led SW module.
2026-05-03 EG-22 LEDs SW module added.
2026-05-05 EG-22 Buzzer SW module implemented, but not tested.
2026-05-09 EG-37 Draft of gateway SW stack.
2026-05-09 EG-22 Enable the buzzer.
2026-05-10 EG-37 Made connections transparent.
2026-05-16 EG-22 Enter and exit configuration mode working.
2026-05-17 EG-22 Able to receive frames packets.
2026-05-17 EG-22 Pair and unpair functionality, with bugs.
2026-05-17 EG-22 Adding, removing sensors and update status of sensors is implemented.
2026-05-19 EG-22 Detect open windows.
2026-05-19 EG-22 Fixed bugs from reed switch code enable.
2026-05-19 EG-22 All functionality implemented but not fully tested.
2026-05-21 EG-22 Bug fixed: number of sensors in header updated.
2026-05-21 EG-22 Bug fix: at startup can trigger an alert.
2026-05-21 EG-22 Deleted includes of already deleted header files.
2026-05-23 EG-22 Sensor low battery handled.
2026-05-28 EG-22 Independent watchdog enabled.
2026-05-28 EG-22 Entire code documented with doxygen.
2026-06-13 EG-43 RF and sensor design decisions. Missing sensor antenna and CC1101 balun. Missing electronic enclosure.
2026-06-14 EG-43 Balun for 868 MHz.
2026-06-20 EG-43 Antenna and electronics enclosure information.
2026-06-20 EG-43 Gateway design decisions updated for REV2.0
2026-06-24 EG-49 Initial REV1.0 project, from REV0.0.
2026-06-25 EG-49 Base the sensor REV1.0 on gateway REV1.0.
2026-06-25 EG-49 Update the spending doc.
2026-06-25 EG-49 Several components addes, such as bulk capacitors, battery holder, MCU and reed switches.
